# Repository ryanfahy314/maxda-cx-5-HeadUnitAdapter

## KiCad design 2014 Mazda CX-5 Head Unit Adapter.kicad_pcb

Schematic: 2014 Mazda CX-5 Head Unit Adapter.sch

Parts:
J1: MX49_USB_Connector; JAE_MX49
J2: 1-1612048-0; TE_Conn_24pin_1612048
J3: AudioJack3; CUI_SJ1-3523N
J4: USB_A; TE_292303-1
R1: 0; R_0805_2012Metric_Pad1.15x1.40mm_HandSolder

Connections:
AUX_GND: J2.X, J3.S
AUX_Left: J2.Z, J3.T
AUX_Right: J2.Y, J3.R
unnamed: J4.SH1, R1.1
USB_D+: J1.B, J4.3
USB_D-: J1.D, J4.2
USB_GND: J1.A, J4.4, R1.2
USB_PWR: J1.C, J4.1

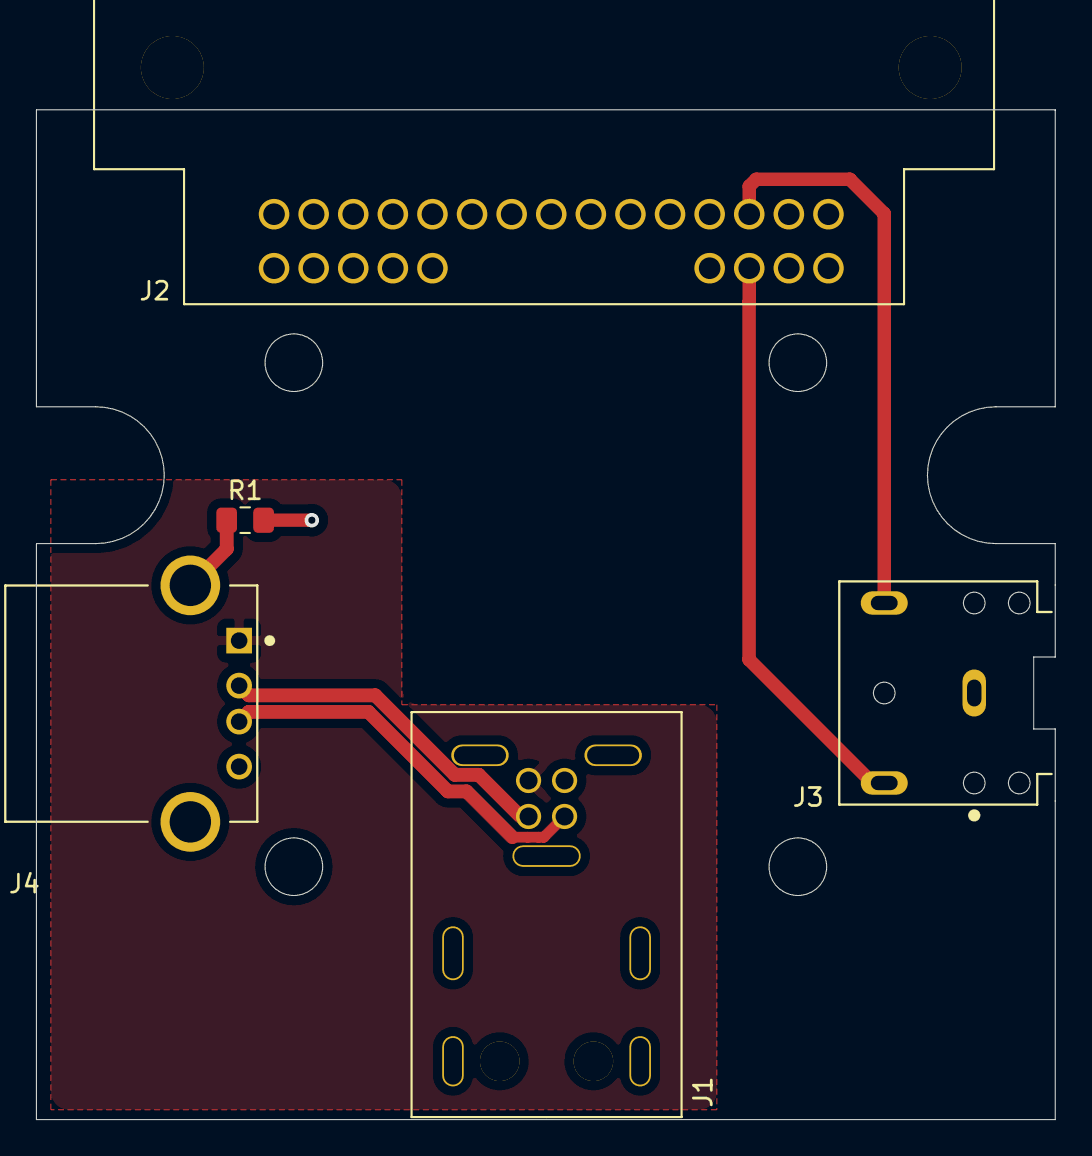
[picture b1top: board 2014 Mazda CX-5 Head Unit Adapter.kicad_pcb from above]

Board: 2 copper layers, 56.6 x 56.1 mm, 5 parts (0 on the bottom side), 8 nets.

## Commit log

2023-01-20 2022-05-27 Revision B
